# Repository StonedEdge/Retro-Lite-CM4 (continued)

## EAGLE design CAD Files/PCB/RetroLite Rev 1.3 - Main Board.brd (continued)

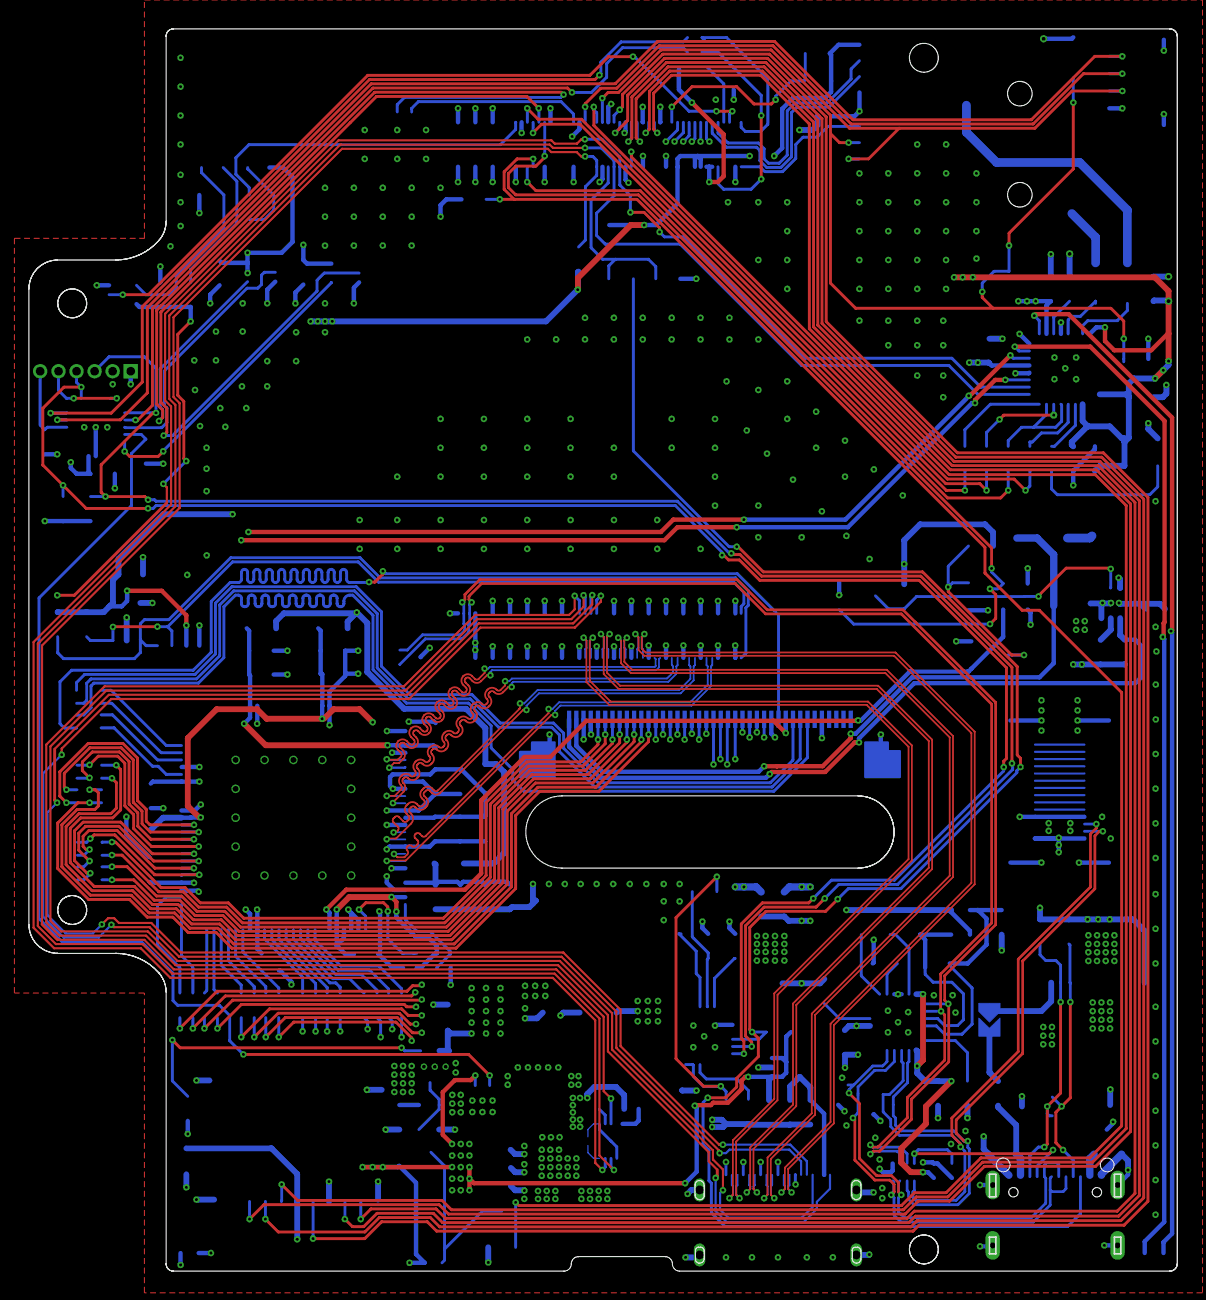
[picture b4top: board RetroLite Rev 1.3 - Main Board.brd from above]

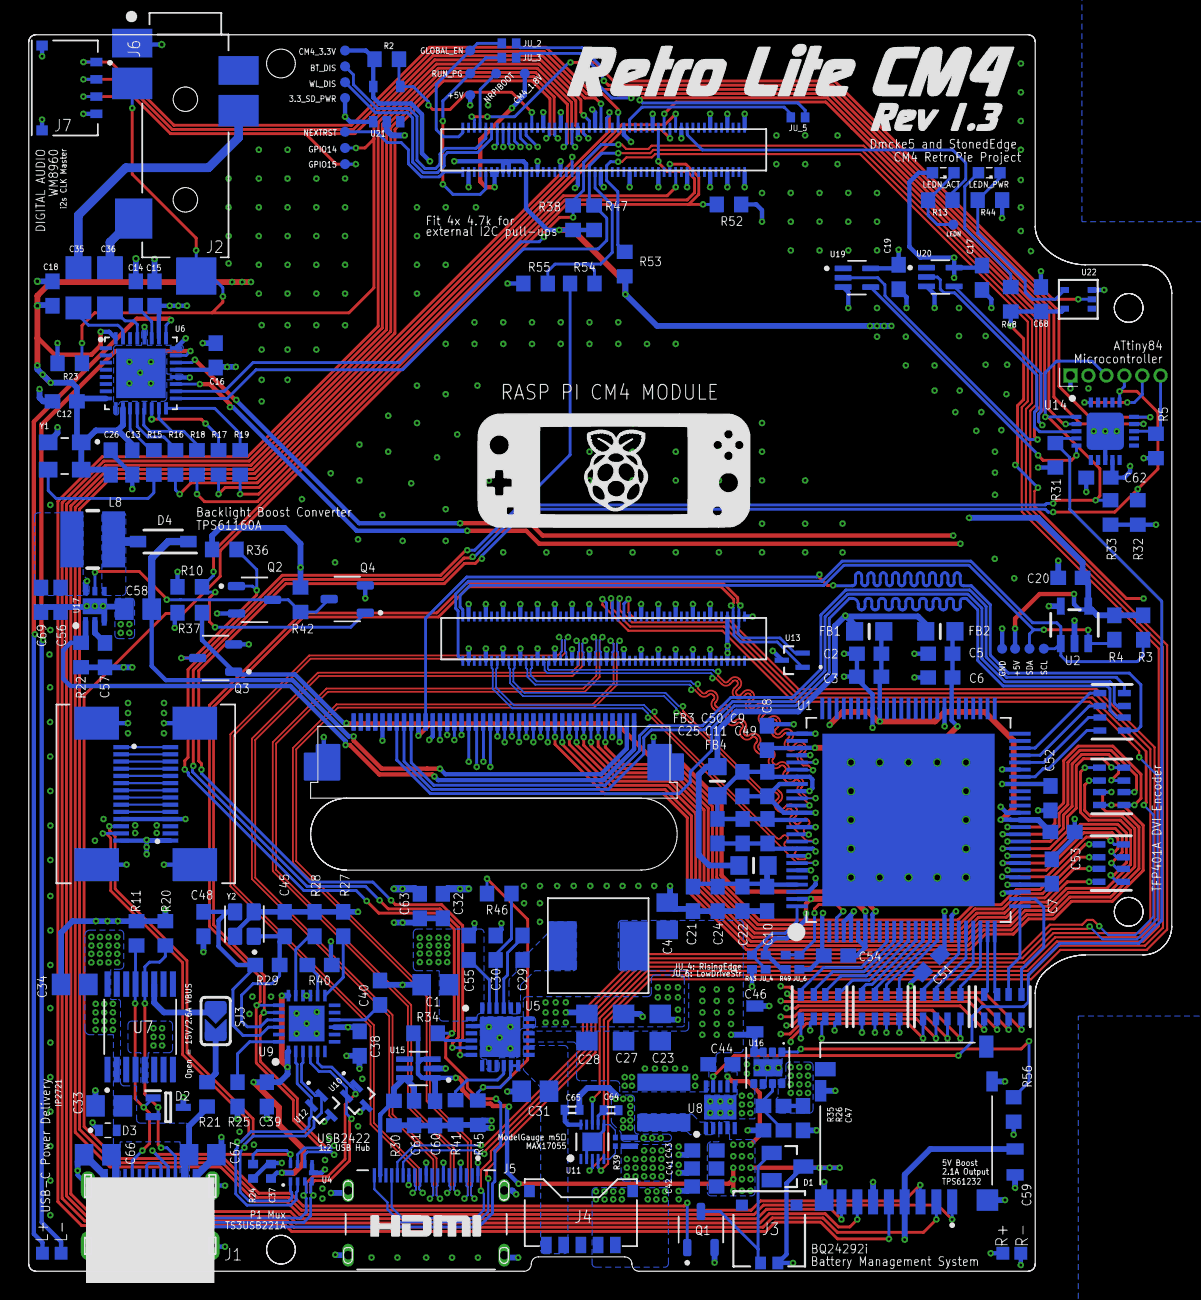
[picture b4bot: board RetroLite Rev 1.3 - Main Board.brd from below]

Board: 4 copper layers, 79.4 x 85.9 mm, 202 parts (201 on the bottom side), 200 nets.

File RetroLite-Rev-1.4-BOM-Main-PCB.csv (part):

Qty,Available,Value,Device,Package,Board Desginator,Voltage Rating ,Power Rating,Description,Additional Notes to PCBA House,Manufacturer Part Number,Unit Price,Total Price,SMT,THT,Original,Remark
1,YES,N/A,LEDSML0603,603,LEDN_ACT,>3.3V,<1W,Green LED,,Generic/Cheapest OK,0.030 ,0.030 ,2 ,,N,
1,YES,N/A,LEDSML0603,603,LEDN_PWR,>3.3V,<1W,Red LED,,Generic/Cheapest OK,0.030 ,0.030 ,2 ,,N,New added 20211124
6,YES,0,R-EU_R0402,402,"JU_1, JU_2, JU_3, JU_4, JU_5, JU_6 ",,1/8W or 1/4W,Resistor Jumper,,Generic/Cheapest OK,0.000 ,0.000 ,12 ,,N,
16,YES,0.01uF,CAP_CERAMIC0603_NO,603,"C2, C3, C5, C6, C7, C8, C9, C10, C11, C21, C22, C25, C49, C51, C53, C54",>16V,CAP CER SMD 0603 .01UF 10% X7R,Capacitor,,Generic/Cheapest OK,0.000 ,0.000 ,32 ,,N,
1,YES,0.047uF,C-EUC0603,603,C29,>50V,CAP CER 0.047UF 50V X7R 0603,Capacitor,,Generic/Cheapest OK,0.000 ,0.000 ,2 ,,N,
1,YES,0.1uF,0.1UF-0603-25V-(+80/-20%),402,C37,>10V,CAP CER 1UF 10V X5R 0603,Capacitor,,Generic/Cheapest OK,0.000 ,0.000 ,2 ,,N,
1,YES,0.1uF,C-EUC0402,402,C65,>10V,CAP CER 0.1UF 10V X5R 0402,Capacitor,,Generic/Cheapest OK,0.000 ,0.000 ,2 ,,N,
7,?,0.1uF,C-EUC0603,603,"C12, C13, C17, C18, C19, C26, C62 ",>10V,CAP CER 0.1UF 10V X5R 0603,Capacitor,,Generic/Cheapest OK,0.000 ,0.000 ,14 ,,N,
1,?,0.1uF,CAP_CERAMIC0603_NO,603,C20,>10V,CAP CER 0.1UF 10V X5R 0603,Capacitor,,Generic/Cheapest OK,0.000 ,0.000 ,2 ,,N,
1,YES,0.47uF,C-EUC0402,402,C64,>25V,CAP CER 0.47UF 25V X5R 0402 ,Capacitor,,Generic/Cheapest OK,0.000 ,0.000 ,2 ,,N,
2,YES,1-1734839-4,1-1734839-4,TE_1-1734839-4,"LEFTPCB, RIGHTPCB",,,"Connectors (Controller, Left & Right)",,Generic/Cheapest OK,1.081 ,2.162 ,28 ,,Y,Change to original
6,YES,1.0uF,1.0UF-0603-16V-10%,603,"C41, C42, C43, C44, C47, C68",>10V,CAP CER 1UF 10V X5R 0603 ,Capacitor,,Generic/Cheapest OK,0.020 ,0.120 ,12 ,,N,
1,?,100k,100KOHM-0603-1/10W-1%,402,R24,,1/10W,Resistor,,Generic/Cheapest OK,0.020 ,0.020 ,2 ,,N,
1,YES,100k,R-EU_R0603,603,R21,,1/8W or 1/4W,Resistor,,Generic/Cheapest OK,0.000 ,0.000 ,2 ,,N,1/10W
1,YES,100nF,C-EUC0603,603,C39,>16V,CAP CER 0.1UF 16V X7R 0603,Capacitor,,Generic/Cheapest OK,0.000 ,0.000 ,2 ,,N,
2,NO,100uF,C-EUC1206,1206,"C35, C36",>4V,CAP CER 100UF 4V X6S 1206,Capacitor,,Generic/Cheapest OK,0.280 ,0.560 ,4 ,,N,
1,?,33k,R-EU_R0603,603,R23,,1/10W,Resistor,,Generic/Cheapest OK,0.000 ,0.000 ,2 ,,N,
5,YES,10,R-EU_R0603,603,"R15, R16, R17, R18, R19",,1/8W or 1/4W,Resistor,,Generic/Cheapest OK,0.000 ,0.000 ,10 ,,N,1/10W
2,YES,10k,R-EU_R0402,402,"R43, R49",,1/8W or 1/4W,Resistor,,Generic/Cheapest OK,0.000 ,0.000 ,4 ,,N,1/16W
9,YES,10k,R-EU_R0603,603,"R10, R31, R34, R36, R37, R42, R44, R52, R56",,1/8W or 1/4W,Resistor,,Generic/Cheapest OK,0.000 ,0.000 ,18 ,,N,1/10W
2,YES,10k,R-EU_R0603,603,"R45, R46",,1/8W or 1/4W,Resistor,,Generic/Cheapest OK,0.000 ,0.000 ,4 ,,N,1/10W
2,YES,10uF,1.0UF-0805-25V-(+80/-20%),805,"C46, C59",>6.3V,CAP CER 10UF 6.3V X5R 0805,Capacitor,,Generic/Cheapest OK,0.020 ,0.040 ,4 ,,N,
2,YES,10uF,C-EUC0805,805,"C66, C67",>6.3V,CAP CER 10UF 6.3V X5R 0805,Capacitor,,Generic/Cheapest OK,0.020 ,0.040 ,4 ,,N,
5,YES,10uF,C-EUC0805,805,"C4, C23, C27, C28, C31",>6.3V,CAP CER 10UF 6.3V X5R 0805,Capacitor,,Generic/Cheapest OK,0.020 ,0.100 ,10 ,,N,
1,YES,1140084168,1140084168,AMPHENOL_1140084168,M-SD,,CAP CER 10UF 6.3V X5R 0805,Connector,,Generic/Cheapest OK,0.950 ,0.950 ,14 ,,N,
1,?,12k,12KOHM-0603-1/10W-1%,603,R25,,1/10W,Resistor,,Generic/Cheapest OK,0.000 ,0.000 ,2 ,,N,
1,YES,12k,R-EU_R0603,603,R2,,1/8W or 1/4W,Resistor,,Generic/Cheapest OK,0.000 ,0.000 ,2 ,,N,1/10W
1,YES,15k,R-EU_R0603,603,R55,,1/8W or 1/4W,Resistor,,Generic/Cheapest OK,0.000 ,0.000 ,2 ,,N,1/10W
1,YES,162k,R-US_R0603,603,R35,,1/8W or 1/4W,Resistor,,Generic/Cheapest OK,0.000 ,0.000 ,2 ,,N,1/10W
1,YES,18nF,CAP_CERAMIC0603_NO,603,C61,>10V,CAP CER 0.018UF 25V X7R 0603,Capacitor,,Generic/Cheapest OK,0.000 ,0.000 ,2 ,,N,
2,YES,18pF,C-EUC0603,603,"C45, C48",>10V,CAP CER 18PF 25V 0603,Capacitor,,Generic/Cheapest OK,0.000 ,0.000 ,4 ,,N,
1,?,1k,R-US_R0603,603,R30,,1/10W,Resistor,,Generic/Cheapest OK,0.000 ,0.000 ,2 ,,N,
2,YES,1k,R-EU_R0603,603,"R13, R54",,1/8W or 1/4W,Resistor,,Generic/Cheapest OK,0.000 ,0.000 ,4 ,,N,1/10W
4,YES,1uF,C-EUC0603,603,"C30, C38, C40, C55",>10V,CAP CER 1UF 10V X5R 0603,Capacitor,,Generic/Cheapest OK,0.012 ,0.048 ,8 ,,N,
2,YES,1uF,C-EUC0805,805,"C33, C34",>25V,CAP CER 1UF 25V X7R 0805,Capacitor,,Generic/Cheapest OK,0.015 ,0.030 ,4 ,,N,
3,YES,1uF,CAP_CERAMIC0603_NO,603,"C32, C60, C63",>10V,CAP CER 1UF 10V X5R 0603,Capacitor,,Generic/Cheapest OK,0.012 ,0.036 ,6 ,,N,
2,YES,1uF,C-EUC0603,603,"C56, C69",>10V,CAP CER 1UF 10V X5R 0603,Capacitor,,Generic/Cheapest OK,0.012 ,0.024 ,4 ,,N,
1,YES,1uF,C-EUC0805,805,C1,>25V,CAP CER 1UF 25V X7R 0805,Capacitor,,Generic/Cheapest OK,0.015 ,0.015 ,2 ,,N,
1,?,2.2k,R-EU_R0603,603,R48,,1/10W,Resistor,,Generic/Cheapest OK,0.000 ,0.000 ,2 ,,N,
1,YES,2026560021,2026560021,CONN_2026560021_MOL,J3,,,Fan Connector,,2026560021,0.620 ,0.620 ,4 ,,Y,
1,YES,220nF,C-EUC0603,603,C57,>10V,CAP CER 0603 220NF 16V X7R 10%,Capacitor,,Generic/Cheapest OK,0.000 ,0.000 ,2 ,,N,
3,YES,22uF,CAP_CERAMIC0603_NO,603,"C24, C50, C52",>6.3V,CAP CER 22UF 6.3V X5R 0603,Capacitor,,Generic/Cheapest OK,0.100 ,0.300 ,6 ,,N,
1,YES,22uH,VLCF4020T-220MR56,VLCF4020_1,L8,,CAP CER 22UF 6.3V X5R 0603,TDK VLCF4020 Series Shielded Wire-wound SMD Inductor 22 uH +/-20% 800mA,,VLCF4020T-220MR56,0.960 ,0.960 ,2 ,,Y,
1,NO,24LC02BT-I/OT,EEPROM_I2C_MCP24AA32,SOT23-5,U2,,,Microchip 32K (4K x 8) 1.8V I2C EEPROM,"https://www.digikey.com/en/products/detail/microchip-technol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
This should work as an alternative…",24LC02BT-I/OT,,,,,,change to DNI 20220528
1,YES,261,R-EU_R0603,603,R41,,1/8W or 1/4W,Resistor,,Generic/Cheapest OK,0.000 ,0.000 ,2 ,,N,1/10W
7,YES,33,CAT16-330J4LFCT-ND,CAT16-330J4LFCT-ND,"R1, R6, R7, R8, R9, R12, R14",,1/8W or 1/4W,Resistor,RES ARRAY 4 RES 33 OHM 1206,Generic/Cheapest OK,0.020 ,0.140 ,56 ,,N,1/10W
6,YES,4.7k,R-EU_R0603,603,"R5, R32, R33, R38, R47, R53",,1/8W or 1/4W,Resistor,,Generic/Cheapest OK,0.000 ,0.000 ,12 ,,N,1/10W
2,YES,4.7k,RESISTOR_0603_NOOUT,603,"R3, R4",,1/8W or 1/4W,Resistor,,Generic/Cheapest OK,0.000 ,0.000 ,4 ,,N,1/10W
3,YES,4.7uF,C-EUC0603,603,"C14, C15, C16",>10V,CAP CER 4.7UF 10V X5R 0603,Capacitor,,Generic/Cheapest OK,0.050 ,0.150 ,6 ,,N,
1,?,4.7uF 50v,C-EUC0603,805,C58,>10V,CAP CER 4.7UF 10V X5R 0603,Capacitor,,Generic/Cheapest OK,0.050 ,0.050 ,2 ,,N,10V
2,YES,5.1k,R-EU_R0603,603,"R11, R20",,1/8W or 1/4W,Resistor,,Generic/Cheapest OK,0.000 ,0.000 ,4 ,,N,1/10W
1,YES,510k,R-US_R0603,603,R26,,1/8W or 1/4W,Resistor,,Generic/Cheapest OK,0.000 ,0.000 ,2 ,,N,1/10W
4,YES,56k,100KOHM-0603-1/10W-1%,603,"R27, R28, R29, R40",,1/8W or 1/4W,Resistor,,Generic/Cheapest OK,0.000 ,0.000 ,8 ,,N,1/10W
1,NO,5,R-EU_R0603,603,R22,,1/8W or 1/4W,Resistor,Ensure tolerance <0.1%. TPS61160A boost converter sense resistor for backlight. Range can be between 4.9 ohms and 5.5 ohms. Please find what is available.,Generic/Cheapest OK ,0.890 ,0.890 ,2 ,,Y,Price based on CPF0603B5R1E1
1,YES,685119136923,685119136923,WURTH_685119136923,J5,,,Mini HDMI Connector,,685119136923,3.941 ,3.941 ,19 ,4 ,Y,
1,YES,78171-0005,78171-0005,MOLEX_78171-0005,J4,,,Pico EZ Mate Battery Connector,,781710005,0.625 ,0.625 ,5 ,,Y,
4,YES,DMN3730-U7,DMN3730-U7,SOT95P280X125-3N,"Q1, Q2, Q3, Q4",,,Mosfets,,DMN3730U-7,0.300 ,1.200 ,12 ,,Y,
1,YES,ASPI-0630HI,ASPI-0630HI,ASPI-0630HI,L6,,,Inductor,,ASPI-0630HI-2R2M-T15,1.128 ,1.128 ,2 ,,Y,
1,YES,BAS70,BAS70,SOT23,D1,,,Schottky Diode,SCHOTTKY SOT-23 70V 0.07A,Generic/Cheapest OK,0.050 ,0.050 ,3 ,,Y,
1,YES,BQ24292I,BQ24292I,QFN50P400X400X100-25N,U5,,,Battery IC,,BQ24292IRGET,7.741 ,7.741 ,24 ,,Y,
1,YES,BUF-74LVC1G07,BUF-74LVC1G07,BUF-74LVC1G07,U22,,,IC Buffer,,SN74LVC1G07DCKR,1.200 ,1.200 ,5 ,,Y,change to SN74LVC1G07DCKR 20211124
2,YES,DF40C-100DS-0.4V(51),DF40C-100DS-0.4V(51),HRS_DF40C-100DS-0.4V(51),"1-100, 101-200",,,B2B Mezannines ,,DF40C-100DS-0.4V(51),1.500 ,3.000 ,200 ,,N,
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
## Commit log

2021-12-26 Rename ATtiny84 Button Code.cpp to ATtiny84/RetroLiteMonitorScript
2021-12-26 Rename RetroLiteMonitorScript to RetroLiteMonitorScript.cpp
2021-12-26 Rename C Scripts/hdmi_switch.sh to Pi Scripts
2021-12-27 Rename RetroLite-CM4 (6).ino to Controller/ATMEGA32u4.cpp
2021-12-27 Rename Retro Lite STLs/placeholder.txt to CAD Files/placeholder.txt
2021-12-27 Create rgb_triangle
2022-04-09 Update ATMEGA32u4.cpp
    Add DPAD hat mode instead of joystick ranges. Add mouse inputs.
2022-04-10 Create placeholder
2022-04-10 Rename Makefile to Retrolite-OSD/Makefile
2022-04-10 Rename display.h to Retrolite-OSD/display.h
2022-05-18 Update fan code to follow linear ramp-up
    Added a temperature for zero speed and a temperature for full speed. When the temperature is between these two values, the the fan speed linearly increases with temperature. This allows the system to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
2022-06-13 Rename hdmi_switch.sh to Retrolite-OSD/hdmi_switch.sh
2022-06-13 Rename retrolite.c to Retrolite-OSD/retrolite.c
2022-09-06 Fix lowVoltageThreshold to work with OSD menu
2022-09-06 Rename max17055.h to Retrolite-OSD/max17055.h
2022-09-06 Rename config to Retrolite-OSD/config
2022-09-06 Rename keycodes.h to Retrolite-OSD/keycodes.h
2022-09-06 Rename retrolite.h to Retrolite-OSD/retrolite.h
2022-09-06 Add in TTF (time-to-full) function
2022-09-06 Switch TTF with TTE on charge detect
2022-09-06 Fix SoC value when charger connect
2022-09-06 Add local getSOC variable to updateBatteryText()
2022-10-04 Add dock STLs
2022-10-04 Add dock STL files
2022-10-28 Add config.txt
2022-11-11 Retro Lite CM4 main housing .STEP files
2022-11-11 Create Housing
2022-11-11 Create placeholder.txt.
2022-11-11 Rename CAD Files/Retro Lite CM4 Front v1.step to CAD Files/Housing/Retro Lite CM4 Front v1.step
2022-11-11 Rename CAD Files/Trigger Mounts Left.step to CAD Files/Housing/Trigger Mounts Left.step
2022-11-11 Rename CAD Files/Trigger Mounts Right.step to CAD Files/Housing/Trigger Mounts Right.step
2022-11-11 Rename RetroLite-Rev-1.4-BOM-Main-PCB.csv to BOM/RetroLite-Rev-1.4-BOM-Main-PCB.csv
2022-11-11 Rename Retrolite-CM4-Left-PCB.csv to BOM/Retrolite-CM4-Left-PCB.csv
2022-11-11 Rename Retrolite-CM4-Right-PCB.csv to BOM/Retrolite-CM4-Right-PCB.csv
2022-11-11 Rename CAD Files/RetroLite Rev 1.3 - Main Board.brd to CAD Files/PCB/RetroLite Rev 1.3 - Main Board.brd
2022-11-11 Rename Controller/ATMEGA32u4.cpp to HID-Controller/ATMEGA32u4.cpp
2022-11-11 Rename RetroLite-Rev-1.4-BOM-Main-PCB.csv to RetroLite-Rev-1.3-Main-PCB.csv
2022-11-11 Create LICENSE
2023-02-01 Rename Retrolite-OSD/display.h to src/display.h
2023-02-01 Rename Retrolite-OSD/Makefile to src/Makefile
2023-02-01 Rename Retrolite-OSD/config to src/config
2023-02-01 Rename Retrolite-OSD/retrolite.c to src/retrolite.c
2023-02-01 Rename Retrolite-OSD/max17055.h to src/max17055.h
2023-02-01 Rename Retrolite-OSD/hdmi_switch.sh to src/hdmi_switch.sh
2023-02-01 Rename Retrolite-OSD/keycodes.h to src/keycodes.h
2023-02-01 Rename Retrolite-OSD/retrolite.h to src/retrolite.h
2023-02-20 Update TTE/TTF time display functions
2023-02-20 Add TTF declaration
2023-02-20 Add BatteryFullyCharged message to user
2023-02-20 Battery Menu Fix
    Fixed battery menu getting stuck on display when pressing up or down on the dpad whilst menu is open.
2023-02-20 Code Tidy
    Fixed Indentation and formatting errors to keep code style consistent
2023-02-20 Headphone detect oscillation
    Fixed oscillation in the headphone detect code that was filling the terminal with text preventing usage of backend features of retropie
2023-02-20 Removed Unused Variable
2023-02-22 Time to Full/Empty fix
    Added a leading zero to the minutes readout when values are under 10 to more accurately represent a "time"
2023-03-06 Change to full brightness as default
2023-03-06 Change to full brightness as default setting
2023-03-07 Convert vempty to mV
2023-03-12 Config Saving Update
    Truncated the float value that's being saved for lowVoltageThreshold to 1 decimal place.
2023-03-27 Implement hysteresis & PID controller
2023-03-27 Update PID controller
2023-03-27 Update cpuFanThreshold
2023-04-20 getControllerData()
    Created getControllerData function to handle controller serial comms. Checks serial connection before requesting data to avoid crashing. Returns controllerError when no data is available or the contr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
2023-04-20 getControllerData()
    Added some variables in relation to the new getControllerData function
2023-04-20 Fixed missing bracket
2023-04-23 Update retrolite.c
    Added closeSerial command upon controller disconnect
2023-06-06 Rename config.txt to boot/config.txt
2023-06-06 Rename cmdline.txt to boot/cmdline.txt
2023-09-13 Update ATMEGA32u4.cpp
    Joystick LUT overrun issue
2026-05-15 Refactor ATMEGA32u4 firmware for QM-C64 gamepad
    Updated firmware for Retro Lite QM-C64 gamepad, simplifying features and removing unnecessary components
2026-05-15 Enhance ATMEGA32u4 firmware with calibration mode
    Updated the ATMEGA32u4 USB Gamepad firmware to include a calibration mode with detailed steps for users. Improved button handling and joystick input processing.
